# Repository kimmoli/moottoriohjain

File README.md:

Moottoriohjain v1.00
===================

BOM
---

| Qty | Value             | Package         | Locators                                 |
|-----|-------------------|-----------------|------------------------------------------|
| 2   | TBD               | C0603           | C3, C4                                   | 
| 4   | 100n              | C0603           | C5, C12, C13, C14                        | 
| 1   | 10k0              | R0603           | R11                                      | 
| 1   | 10n               | C0603           | C11                                      | 
| 1   | 150µF             | CT7343          | C8                                       | 
| 2   | 1µ                | C0805           | C1, C2                                   | 
| 8   | 2k15              | R0603           | R2, R3, R4, R5, R6, R7, R8, R9           | 
| 4   | 2µ2 50V           | C0805           | C6, C7, C9, C10                          | 
| 6   | 300               | R0603           | R1, R10, R13, R14, R15, R17              | 
| 1   | 3k24              | R0603           | R12                                      | 
| 2   | BTM7710G          | SOIC28-WIDE     | N2, N3                                   | 
| 4   | GRN               | LED0603         | H2, H3, H4, H5                           | 
| 2   | RED               | LED0603         | H1, H6                                   | 
| 1   | LPC812M101JDH16FP | TSSOP16         | D1                                       | 
| 1   | MCP1700T-3302E/TT | SOT23           | N1                                       | 
| 1   | PIIKKIRIMA-1      | PIIKKIRIMA-1    | X5                                       | 
| 1   | PIIKKIRIMA-2      | PIIKKIRIMA-2    | X4                                       | 
| 2   | PIIKKIRIMA-3      | PIIKKIRIMA-3    | X2, X8                                   | 
| 1   | PIIKKIRIMA-5      | PIIKKIRIMA-5    | X1                                       | 
| 1   | STPS340U          | SMB             | V1                                       | 
| 5   | TE 282837-2       | TE_RUUVILIITIN2 | X3, X6, X7, X9, X10                      | 
| 1   | TPS5430DDA        | SOIC8-N-EP      | N4                                       | 
| 1   | VLP8040-47U       | VLP8040         | L2                                       |

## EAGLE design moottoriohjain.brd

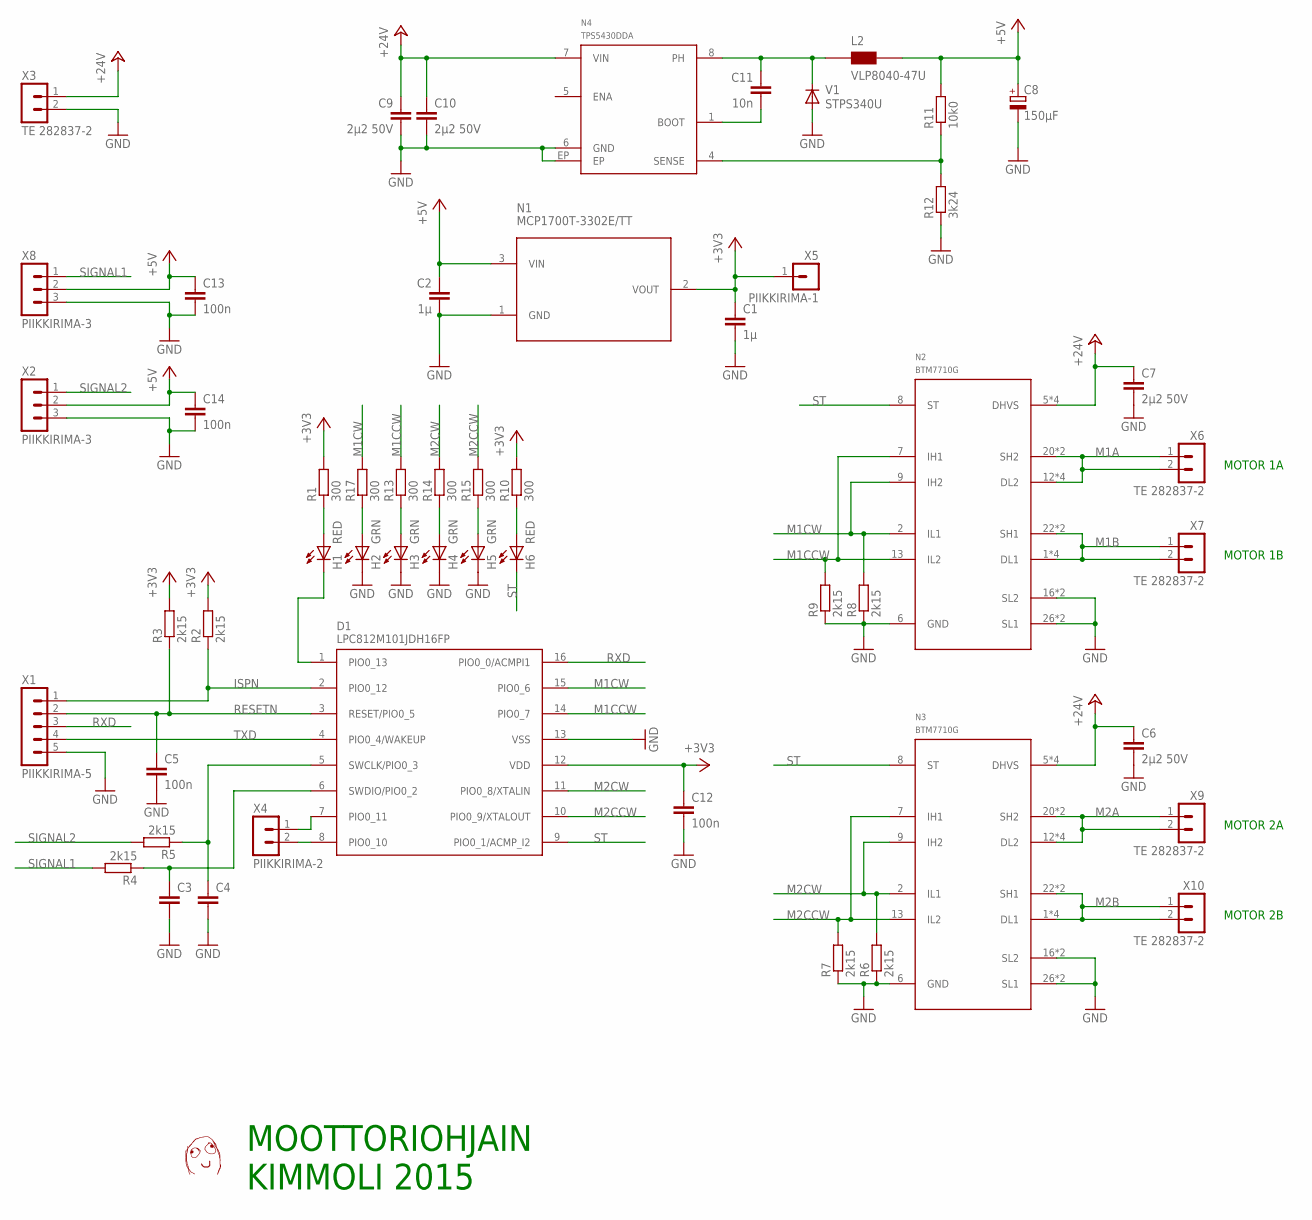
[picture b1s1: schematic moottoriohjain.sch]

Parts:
C1, C2: 1µ; C0805
C3, C4: CAP0603; C0603
C5, C12, C13, C14: 100n; C0603
C6, C7, C9, C10: 2µ2 50V; C0805
C8: 150µF; CT7343
C11: 10n; C0603
D1: LPC812M101JDH16FP; SEB_TSSOP16
H1, H6: RED; CHIP-LED0603
H2, H3, H4, H5: GRN; CHIP-LED0603
L2: VLP8040-47U; VLP8040
N1: MCP1700T-3302E/TT; SOT23
N2, N3: BTM7710G; SOIC28-W_MC
N4: TPS5430DDA; SOIC8-N-EP
R1, R10, R13, R14, R15, R17: 300; R0603
R2, R3, R4, R5, R6, R7, R8, R9: 2k15; R0603
R11: 10k0; R0603
R12: 3k24; R0603
U$1: DAFUG
V1: STPS340U; SMB
X1: PIIKKIRIMA-5
X2, X8: PIIKKIRIMA-3
X3, X6, X7, X9, X10: TE 282837-2; TE_RUUVILIITIN2
X4: PIIKKIRIMA-2
X5: PIIKKIRIMA-1

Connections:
+3V3: C1.1, C12.1, D1.12 (VDD), N1.2 (VOUT), R1.2, R2.2, R3.2, R10.2, X5.1
+5V: C2.1, C8.+, C13.1, C14.1, L2.2 (B), N1.3 (VIN), R11.2, X2.2, X8.2
+24V: C6.1, C7.1, C9.1, C10.1, N2.5 (DHVS), N2.10 (DHVS), N2.19 (DHVS), N2.24 (DHVS), N3.5 (DHVS), N3.10 (DHVS), N3.19 (DHVS), N3.24 (DHVS), N4.7 (VIN), X3.1
GND: C1.2, C2.2, C3.2, C4.2, C5.2, C6.2, C7.2, C8.-, C9.2, C10.2, C12.2, C13.2, C14.2, D1.13 (VSS), H2.C, H3.C, H4.C, H5.C, N1.1 (GND), N2.6 (GND), N2.16 (SL2), N2.17 (SL2), N2.26 (SL1), N2.27 (SL1), N3.6 (GND), N3.16 (SL2), N3.17 (SL2), N3.26 (SL1), N3.27 (SL1), N4.6 (GND), N4.EP, R6.1, R7.1, R8.1, R9.1, R12.1, V1.A, X1.5, X2.3, X3.2, X8.3
ISPN: D1.2 (PIO0_12), R2.1, X1.1
M1A: N2.12 (DL2), N2.14 (DL2), N2.15 (DL2), N2.18 (DL2), N2.20 (SH2), N2.21 (SH2), X6.1, X6.2
M1B: N2.1 (DL1), N2.3 (DL1), N2.22 (SH1), N2.23 (SH1), N2.25 (DL1), N2.28 (DL1), X7.1, X7.2
M1CCW: D1.14 (PIO0_7), N2.7 (IH1), N2.13 (IL2), R9.2, R13.2
M1CW: D1.15 (PIO0_6), N2.2 (IL1), N2.9 (IH2), R8.2, R17.2
M2A: N3.12 (DL2), N3.14 (DL2), N3.15 (DL2), N3.18 (DL2), N3.20 (SH2), N3.21 (SH2), X9.1, X9.2
M2B: N3.1 (DL1), N3.3 (DL1), N3.22 (SH1), N3.23 (SH1), N3.25 (DL1), N3.28 (DL1), X10.1, X10.2
M2CCW: D1.10 (PIO0_9/XTALOUT), N3.7 (IH1), N3.13 (IL2), R7.2, R15.2
M2CW: D1.11 (PIO0_8/XTALIN), N3.2 (IL1), N3.9 (IH2), R6.2, R14.2
unnamed: C3.1, D1.6 (SWDIO/PIO0_2), R4.1
unnamed: D1.1 (PIO0_13), H1.C
unnamed: H1.A, R1.1
unnamed: C4.1, D1.5 (SWCLK/PIO0_3), R5.1
unnamed: D1.8 (PIO0_10), X4.2
unnamed: D1.7 (PIO0_11), X4.1
unnamed: H2.A, R17.1
unnamed: H6.A, R10.1
unnamed: H3.A, R13.1
unnamed: H4.A, R14.1
unnamed: H5.A, R15.1
unnamed: C11.2, N4.1 (BOOT)
unnamed: N4.4 (SENSE), R11.1, R12.2
PH: C11.1, L2.1 (A), N4.8 (PH), V1.C
RESETN: C5.1, D1.3 (RESET/PIO0_5), R3.1, X1.2
RXD: D1.16 (PIO0_0/ACMPI1), X1.3
SIGNAL1: R4.2, X8.1
SIGNAL2: R5.2, X2.1
ST: D1.9 (PIO0_1/ACMP_I2), H6.C, N2.8 (ST), N3.8 (ST)
TXD: D1.4 (PIO0_4/WAKEUP), X1.4

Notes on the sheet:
MOTOR 2A
MOTOR 2B
MOTOR 1A
MOTOR 1B
MOOTTORIOHJAIN
KIMMOLI 2015

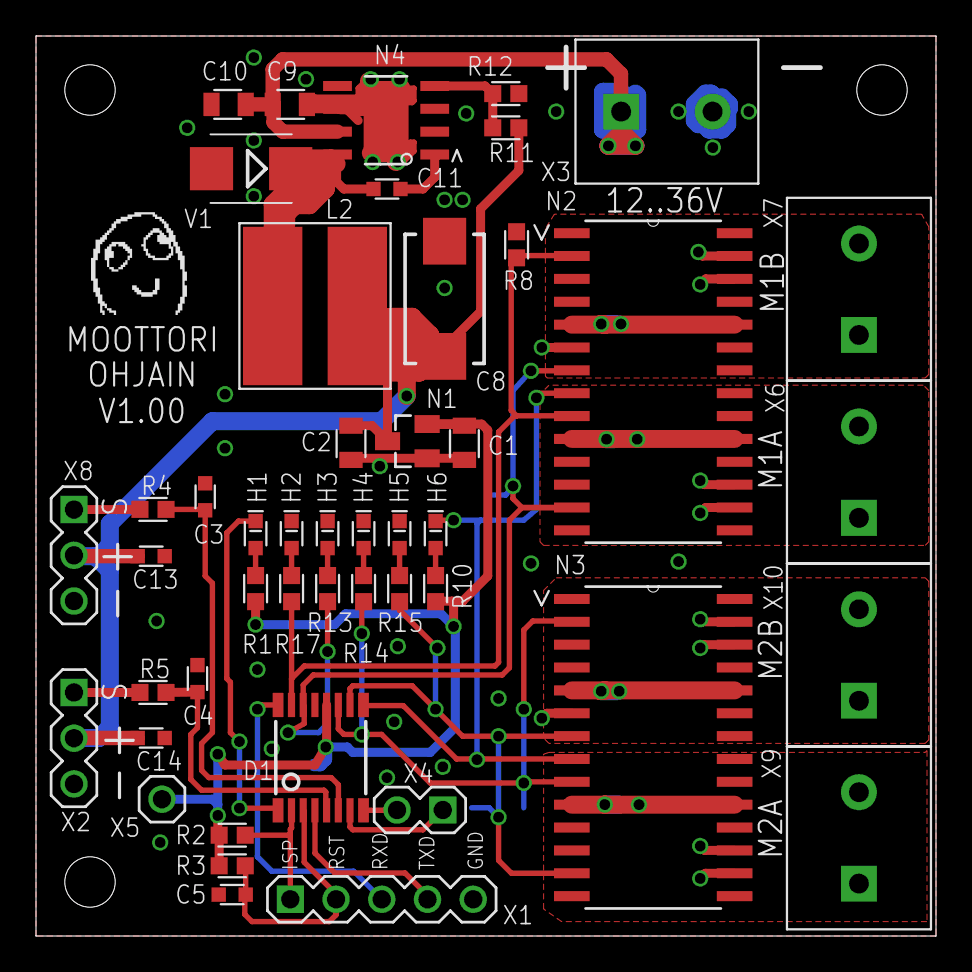
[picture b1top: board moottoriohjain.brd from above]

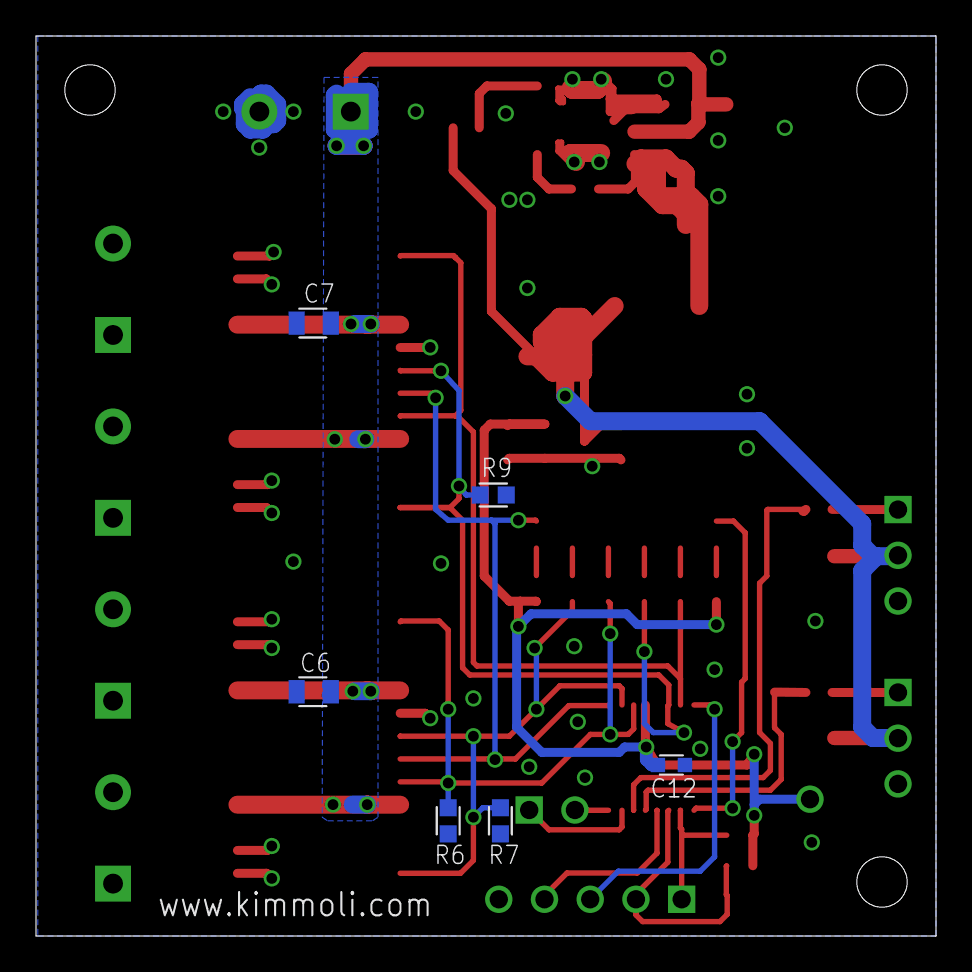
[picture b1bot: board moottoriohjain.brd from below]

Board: 2 copper layers, 50.0 x 50.0 mm, 54 parts (6 on the bottom side), 33 nets.

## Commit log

2015-11-10 initial
